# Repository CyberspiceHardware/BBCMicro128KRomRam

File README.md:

# 128K Sideways ROM/RAM expansion for the BBC Micro

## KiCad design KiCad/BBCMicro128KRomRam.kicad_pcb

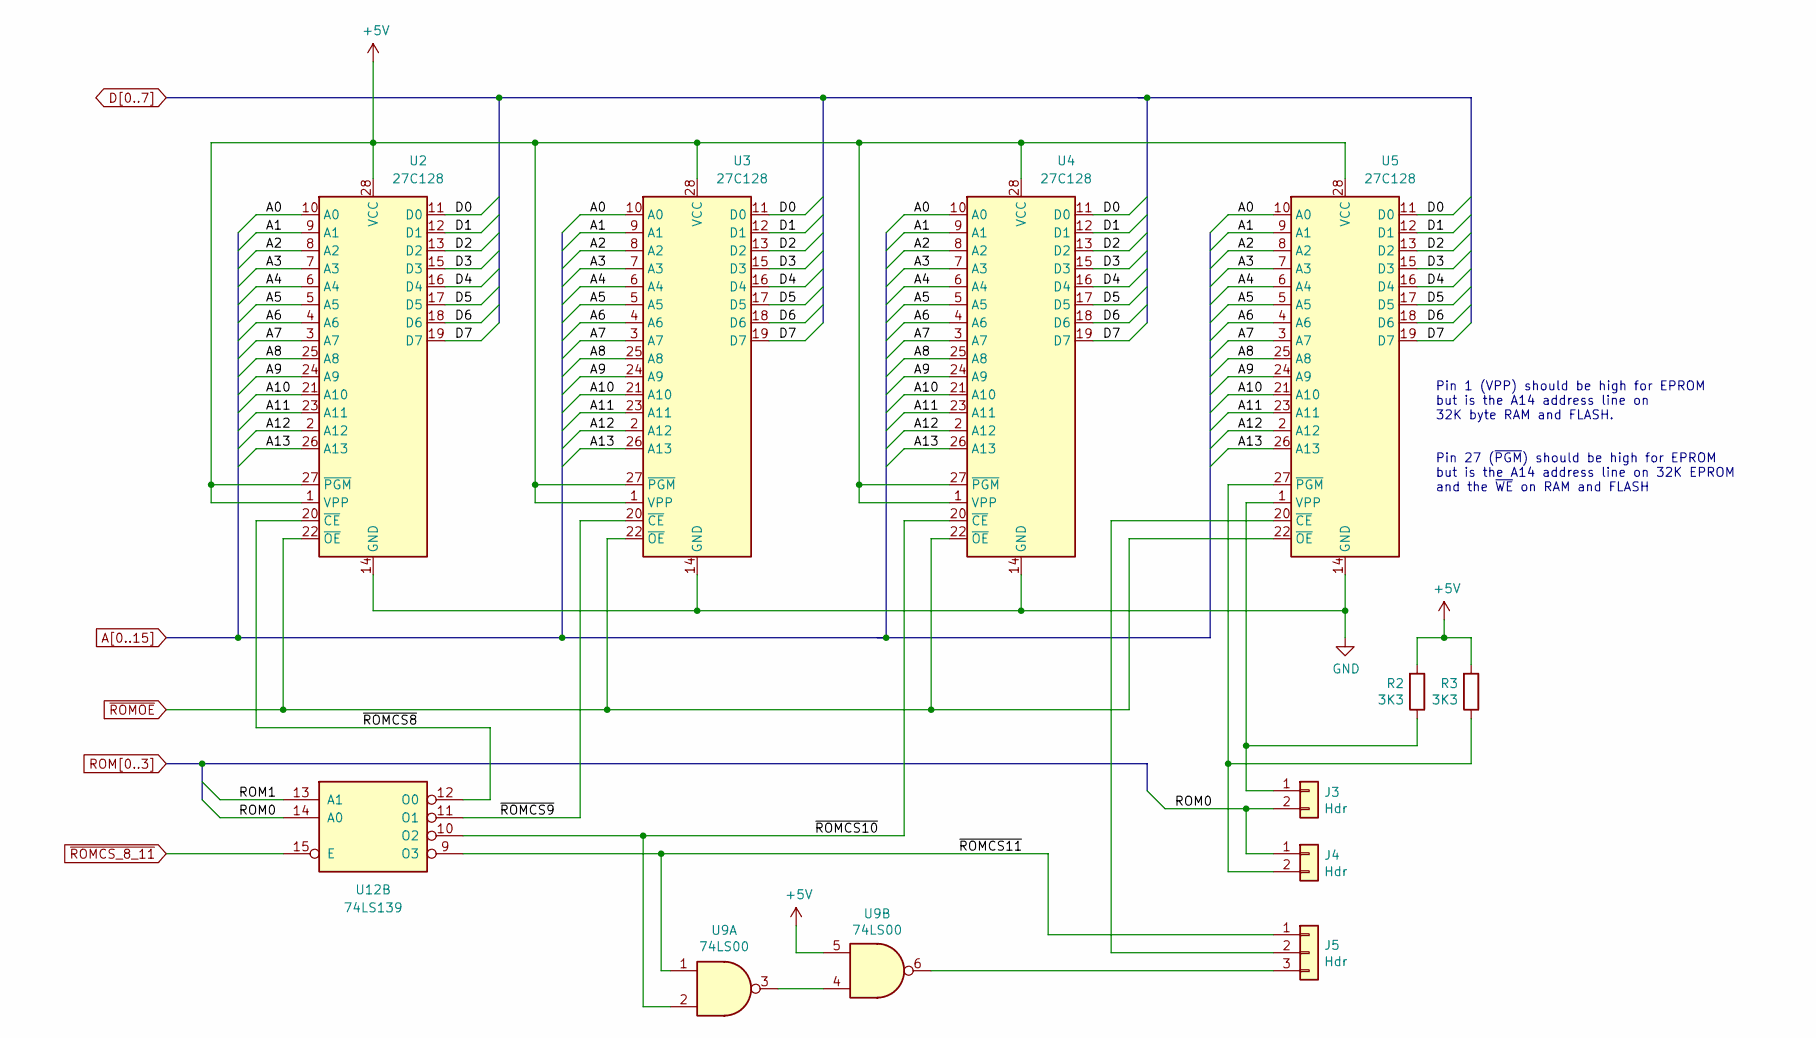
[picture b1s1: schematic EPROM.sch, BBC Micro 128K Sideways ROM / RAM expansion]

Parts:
J3, J4: Hdr; PinHeader_1x02_P2.54mm_Vertical
J5: Hdr; PinHeader_1x03_P2.54mm_Vertical
R2, R3: 3K3; R_Axial_DIN0207_L6.3mm_D2.5mm_P7.62mm_Horizontal
U2, U3, U4, U5: 27C128; DIP-28_W15.24mm_Socket
U9: 74LS00; DIP-14_W7.62mm_Socket
U12: 74LS139

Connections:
+5V: R2.2, R3.2, U2.1 (VPP), U2.27 (~PGM), U2.28 (VCC), U3.1 (VPP), U3.27 (~PGM), U3.28 (VCC), U4.1 (VPP), U4.27 (~PGM), U4.28 (VCC), U5.28 (VCC), U9.5; also elsewhere on the board
/EPROM/~ROMCS8: U2.20 (~CE), U12.12 (O0)
/EPROM/~ROMCS9: U3.20 (~CE), U12.11 (O1)
/EPROM/~ROMCS10: U4.20 (~CE), U9.2, U12.10 (O2)
/EPROM/~ROMCS11: J5.1, U9.1, U12.9 (O3)
A0: U2.10 (A0), U3.10 (A0), U4.10 (A0), U5.10 (A0); also elsewhere on the board
A1: U2.9 (A1), U3.9 (A1), U4.9 (A1), U5.9 (A1); also elsewhere on the board
A2: U2.8 (A2), U3.8 (A2), U4.8 (A2), U5.8 (A2); also elsewhere on the board
A3: U2.7 (A3), U3.7 (A3), U4.7 (A3), U5.7 (A3); also elsewhere on the board
A4: U2.6 (A4), U3.6 (A4), U4.6 (A4), U5.6 (A4); also elsewhere on the board
A5: U2.5 (A5), U3.5 (A5), U4.5 (A5), U5.5 (A5); also elsewhere on the board
A6: U2.4 (A6), U3.4 (A6), U4.4 (A6), U5.4 (A6); also elsewhere on the board
A7: U2.3 (A7), U3.3 (A7), U4.3 (A7), U5.3 (A7); also elsewhere on the board
A8: U2.25 (A8), U3.25 (A8), U4.25 (A8), U5.25 (A8); also elsewhere on the board
A9: U2.24 (A9), U3.24 (A9), U4.24 (A9), U5.24 (A9); also elsewhere on the board
A10: U2.21 (A10), U3.21 (A10), U4.21 (A10), U5.21 (A10); also elsewhere on the board
A11: U2.23 (A11), U3.23 (A11), U4.23 (A11), U5.23 (A11); also elsewhere on the board
A12: U2.2 (A12), U3.2 (A12), U4.2 (A12), U5.2 (A12); also elsewhere on the board
A13: U2.26 (A13), U3.26 (A13), U4.26 (A13), U5.26 (A13); also elsewhere on the board
D0: U2.11 (D0), U3.11 (D0), U4.11 (D0), U5.11 (D0); also elsewhere on the board
D1: U2.12 (D1), U3.12 (D1), U4.12 (D1), U5.12 (D1); also elsewhere on the board
D2: U2.13 (D2), U3.13 (D2), U4.13 (D2), U5.13 (D2); also elsewhere on the board
D3: U2.15 (D3), U3.15 (D3), U4.15 (D3), U5.15 (D3); also elsewhere on the board
D4: U2.16 (D4), U3.16 (D4), U4.16 (D4), U5.16 (D4); also elsewhere on the board
D5: U2.17 (D5), U3.17 (D5), U4.17 (D5), U5.17 (D5); also elsewhere on the board
D6: U2.18 (D6), U3.18 (D6), U4.18 (D6), U5.18 (D6); also elsewhere on the board
D7: U2.19 (D7), U3.19 (D7), U4.19 (D7), U5.19 (D7); also elsewhere on the board
GND: U2.14 (GND), U3.14 (GND), U4.14 (GND), U5.14 (GND); also elsewhere on the board
unnamed: J3.1, R2.1, U5.1 (VPP)
unnamed: J4.2, R3.1, U5.27 (~PGM)
unnamed: J5.2, U5.20 (~CE)
unnamed: J5.3, U9.6
unnamed: U9.3, U9.4
ROM0: J3.2, J4.1, U12.14 (A0); also elsewhere on the board
ROM1: U12.13 (A1); also elsewhere on the board
~ROMCS_8_11: U12.15 (E); also elsewhere on the board
~ROMOE: U2.22 (~OE), U3.22 (~OE), U4.22 (~OE), U5.22 (~OE); also elsewhere on the board

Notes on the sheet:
Pin 1 (VPP) should be high for EPROM but is the A14 address line on 32K byte RAM and FLASH.
Pin 27 (~PGM~) should be high for EPROM but is the A14 address line on 32K EPROM and the ~WE~ on RAM and FLASH

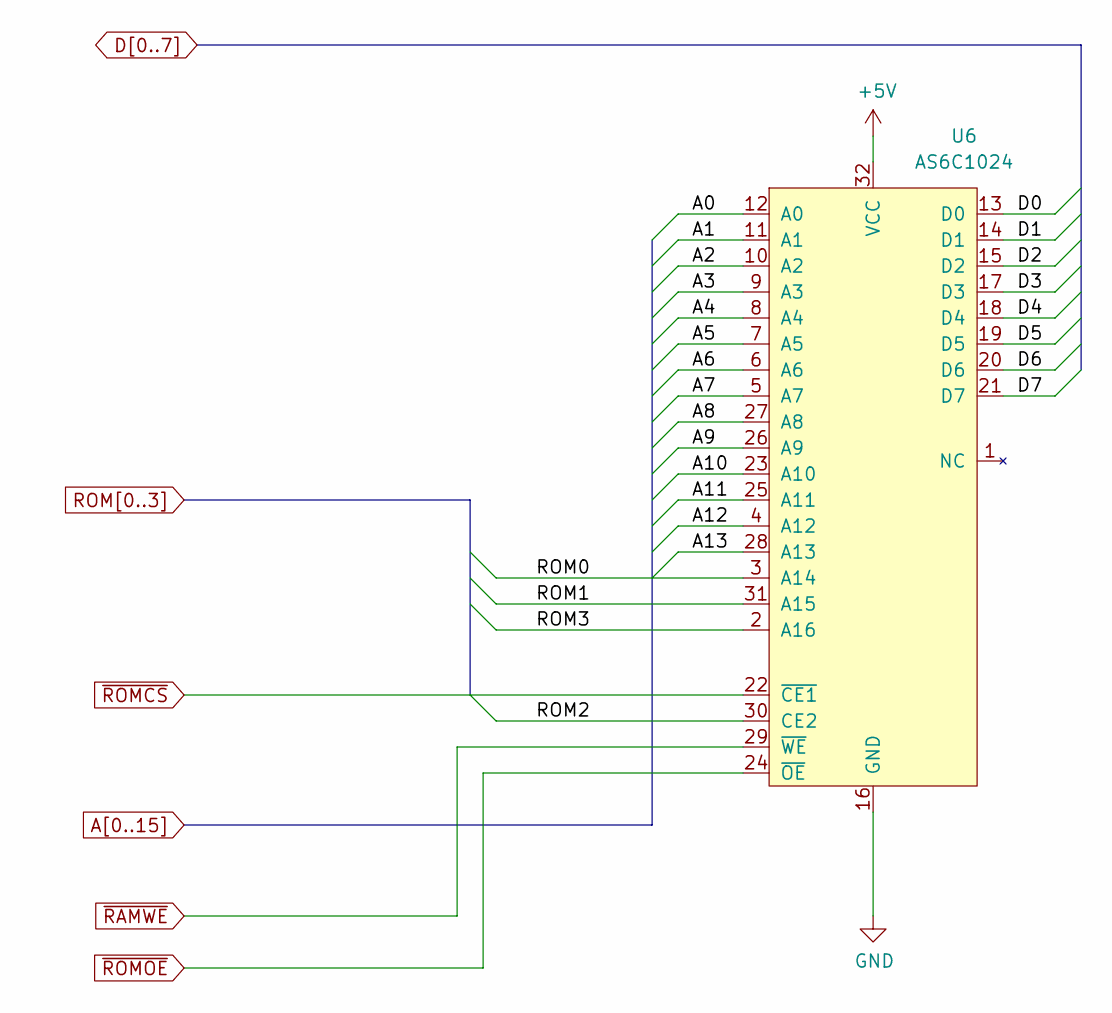
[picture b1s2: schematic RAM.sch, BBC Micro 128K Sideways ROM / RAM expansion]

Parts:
U6: AS6C1024; DIP-32_W15.24mm_Socket

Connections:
+5V: U6.32 (VCC); also elsewhere on the board
A0: U6.12 (A0); also elsewhere on the board
A1: U6.11 (A1); also elsewhere on the board
A2: U6.10 (A2); also elsewhere on the board
A3: U6.9 (A3); also elsewhere on the board
A4: U6.8 (A4); also elsewhere on the board
A5: U6.7 (A5); also elsewhere on the board
A6: U6.6 (A6); also elsewhere on the board
A7: U6.5 (A7); also elsewhere on the board
A8: U6.27 (A8); also elsewhere on the board
A9: U6.26 (A9); also elsewhere on the board
A10: U6.23 (A10); also elsewhere on the board
A11: U6.25 (A11); also elsewhere on the board
A12: U6.4 (A12); also elsewhere on the board
A13: U6.28 (A13); also elsewhere on the board
D0: U6.13 (D0); also elsewhere on the board
D1: U6.14 (D1); also elsewhere on the board
D2: U6.15 (D2); also elsewhere on the board
D3: U6.17 (D3); also elsewhere on the board
D4: U6.18 (D4); also elsewhere on the board
D5: U6.19 (D5); also elsewhere on the board
D6: U6.20 (D6); also elsewhere on the board
D7: U6.21 (D7); also elsewhere on the board
GND: U6.16 (GND); also elsewhere on the board
ROM0: U6.3 (A14); also elsewhere on the board
ROM1: U6.31 (A15); also elsewhere on the board
ROM2: U6.30 (CE2); also elsewhere on the board
ROM3: U6.2 (A16); also elsewhere on the board
~RAMWE: U6.29 (~WE); also elsewhere on the board
~ROMCS: U6.22 (~CE1); also elsewhere on the board
~ROMOE: U6.24 (~OE); also elsewhere on the board

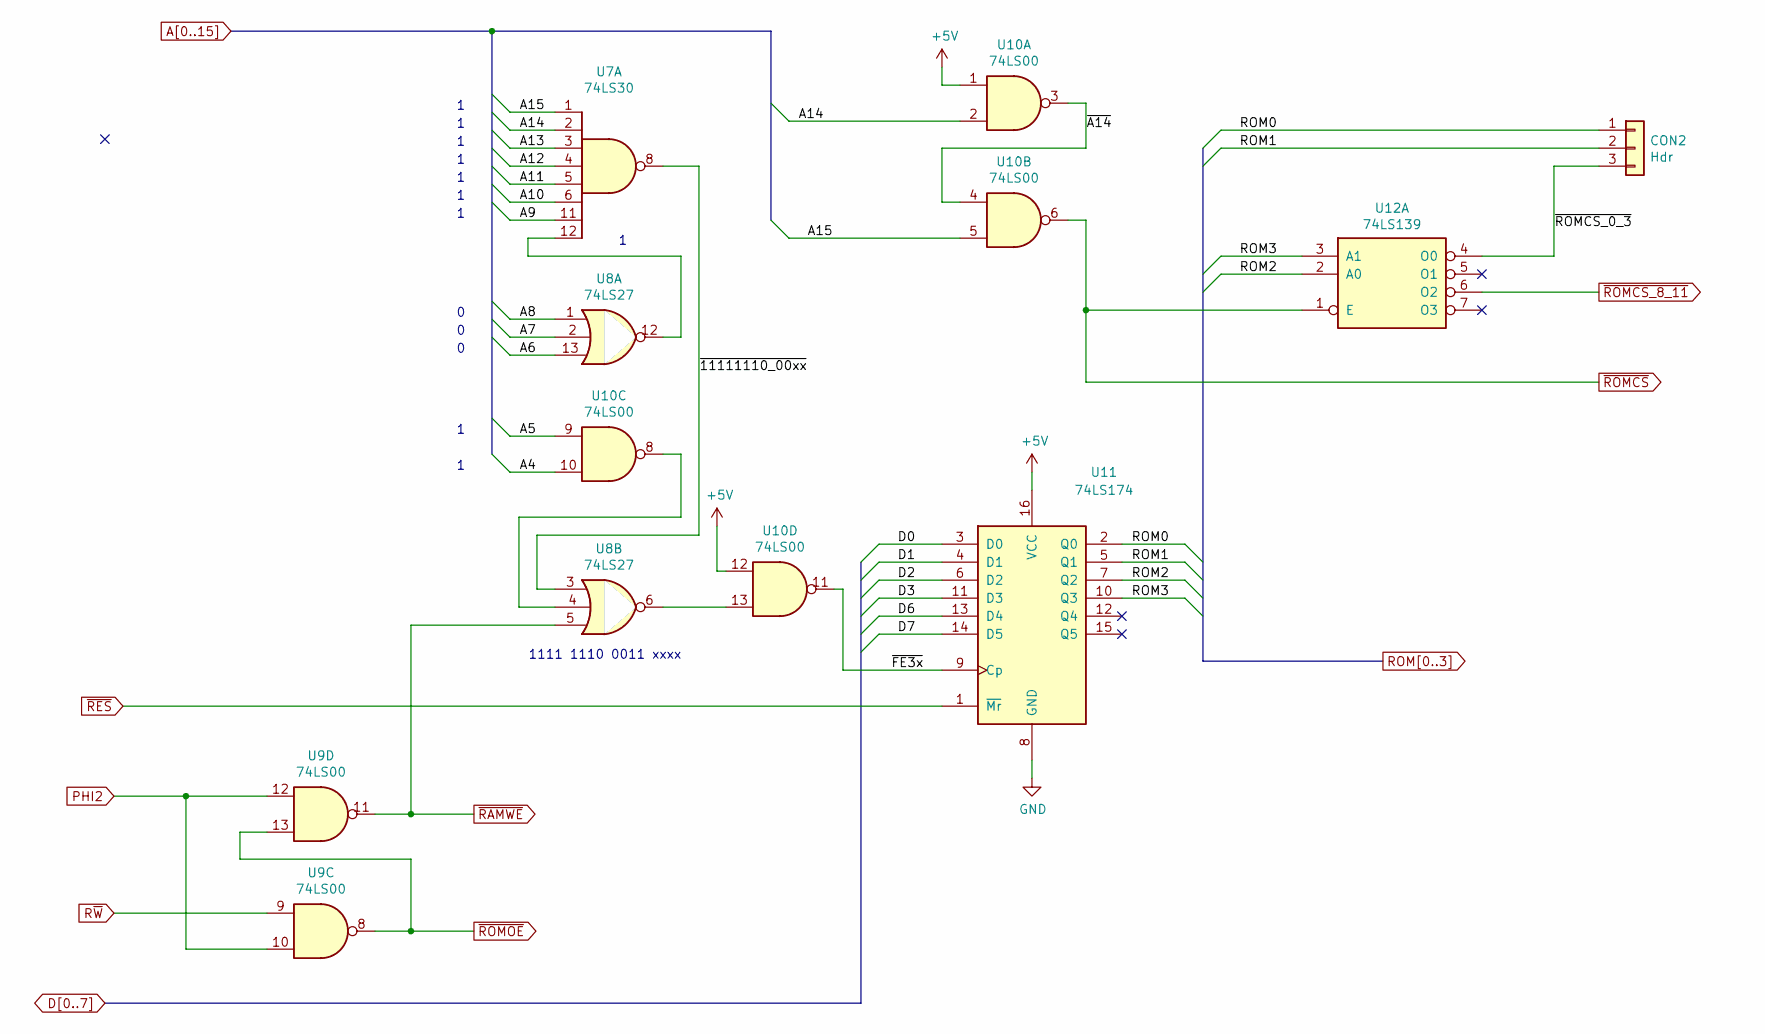
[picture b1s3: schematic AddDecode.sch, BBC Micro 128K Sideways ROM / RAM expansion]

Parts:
CON2: Hdr; PinHeader_1x03_P2.54mm_Horizontal
U7: 74LS30; DIP-14_W7.62mm_Socket
U8: 74LS27; DIP-14_W7.62mm_Socket
U9, U10: 74LS00; DIP-14_W7.62mm_Socket
U11: 74LS174; DIP-16_W7.62mm_Socket
U12: 74LS139; DIP-16_W7.62mm_Socket

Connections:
+5V: U10.1, U10.12, U11.16 (VCC); also elsewhere on the board
/AddDecode/~11111110_00xx: U7.8, U8.3
/AddDecode/~A14: U10.3, U10.4
/AddDecode/~FE3x: U10.11, U11.9 (Cp)
/AddDecode/~ROMCS_0_3: CON2.3, U12.4 (O0)
A4: U10.10; also elsewhere on the board
A5: U10.9; also elsewhere on the board
A6: U8.13; also elsewhere on the board
A7: U8.2; also elsewhere on the board
A8: U8.1; also elsewhere on the board
A9: U7.11; also elsewhere on the board
A10: U7.6; also elsewhere on the board
A11: U7.5; also elsewhere on the board
A12: U7.4; also elsewhere on the board
A13: U7.3; also elsewhere on the board
A14: U7.2, U10.2; also elsewhere on the board
A15: U7.1, U10.5; also elsewhere on the board
D0: U11.3 (D0); also elsewhere on the board
D1: U11.4 (D1); also elsewhere on the board
D2: U11.6 (D2); also elsewhere on the board
D3: U11.11 (D3); also elsewhere on the board
D6: U11.13 (D4); also elsewhere on the board
D7: U11.14 (D5); also elsewhere on the board
GND: U11.8 (GND); also elsewhere on the board
unnamed: U7.12, U8.12
unnamed: U8.4, U10.8
unnamed: U8.6, U10.13
PHI2: U9.10, U9.12; also elsewhere on the board
ROM0: CON2.1, U11.2 (Q0); also elsewhere on the board
ROM1: CON2.2, U11.5 (Q1); also elsewhere on the board
ROM2: U11.7 (Q2), U12.2 (A0); also elsewhere on the board
ROM3: U11.10 (Q3), U12.3 (A1); also elsewhere on the board
R~W: U9.9; also elsewhere on the board
~RAMWE: U8.5, U9.11; also elsewhere on the board
~RES: U11.1 (~Mr); also elsewhere on the board
~ROMCS: U10.6, U12.1 (E); also elsewhere on the board
~ROMCS_8_11: U12.6 (O2); also elsewhere on the board
~ROMOE: U9.8, U9.13; also elsewhere on the board

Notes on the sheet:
1111 1110 0011 xxxx

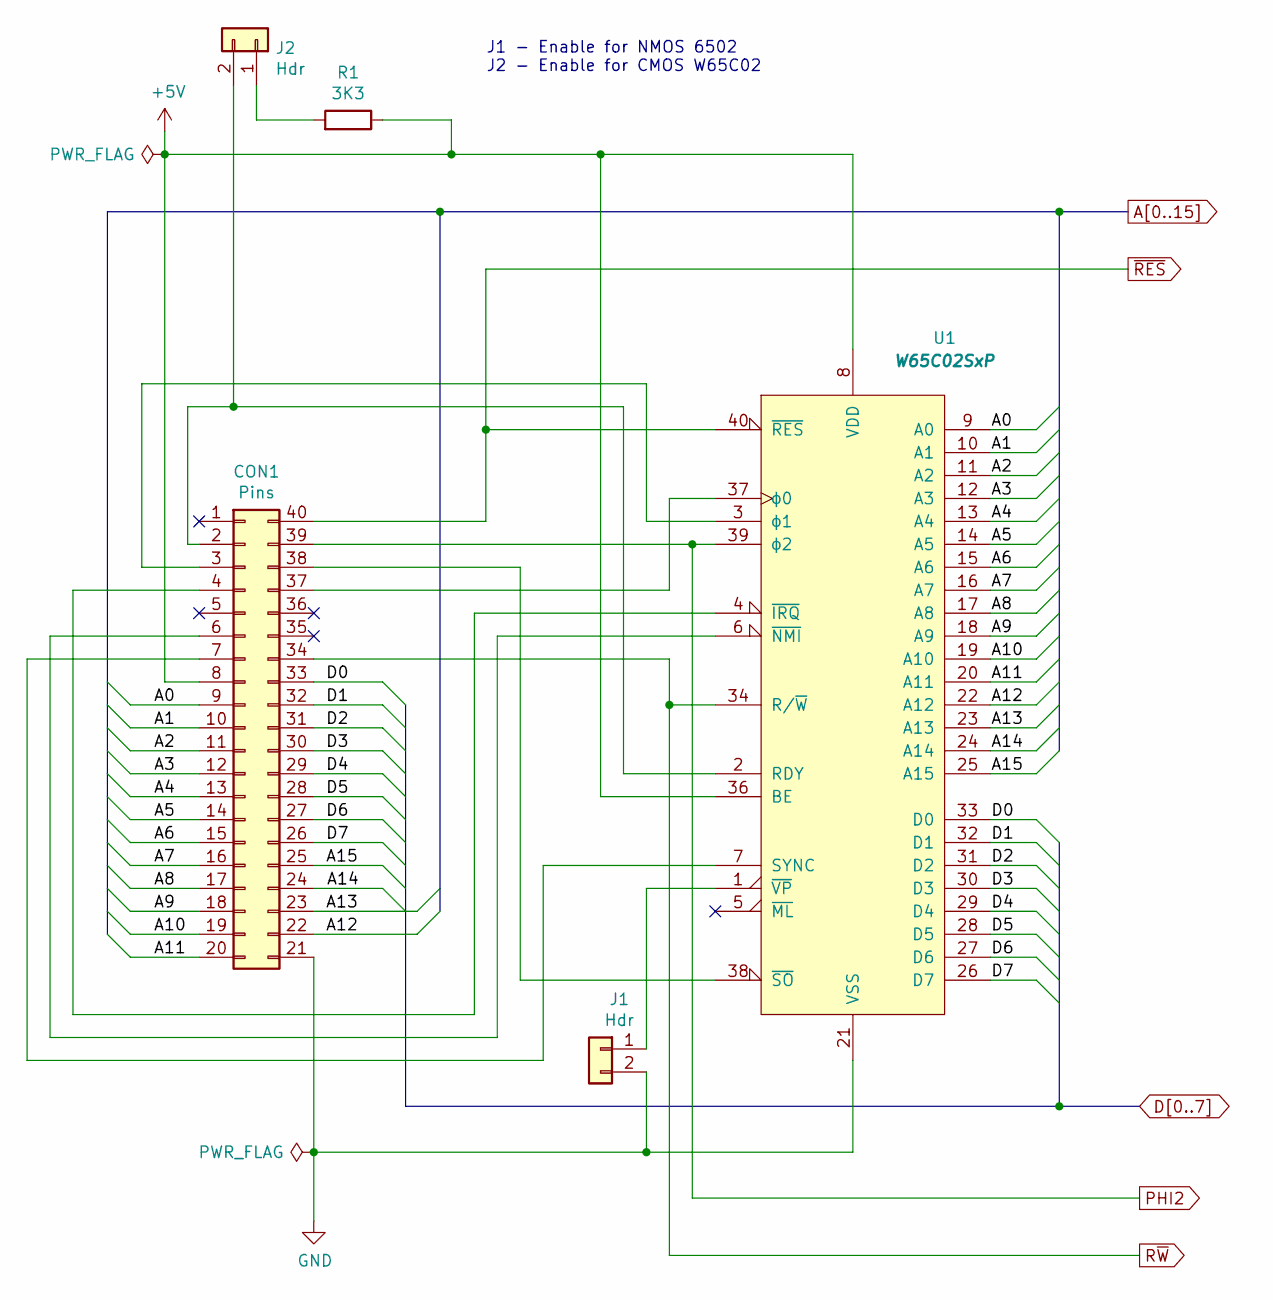
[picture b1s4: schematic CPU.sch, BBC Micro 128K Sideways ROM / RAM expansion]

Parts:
CON1: Pins; DIP-40_W15.24mm_Socket
J1, J2: Hdr; PinHeader_1x02_P2.54mm_Vertical
R1: 3K3; R_Axial_DIN0207_L6.3mm_D2.5mm_P7.62mm_Horizontal
U1: W65C02SxP; DIP-40_W15.24mm_Socket

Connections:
+5V: CON1.8, R1.1, U1.8 (VDD), U1.36 (BE); also elsewhere on the board
A0: CON1.9, U1.9 (A0); also elsewhere on the board
A1: CON1.10, U1.10 (A1); also elsewhere on the board
A2: CON1.11, U1.11 (A2); also elsewhere on the board
A3: CON1.12, U1.12 (A3); also elsewhere on the board
A4: CON1.13, U1.13 (A4); also elsewhere on the board
A5: CON1.14, U1.14 (A5); also elsewhere on the board
A6: CON1.15, U1.15 (A6); also elsewhere on the board
A7: CON1.16, U1.16 (A7); also elsewhere on the board
A8: CON1.17, U1.17 (A8); also elsewhere on the board
A9: CON1.18, U1.18 (A9); also elsewhere on the board
A10: CON1.19, U1.19 (A10); also elsewhere on the board
A11: CON1.20, U1.20 (A11); also elsewhere on the board
A12: CON1.22, U1.22 (A12); also elsewhere on the board
A13: CON1.23, U1.23 (A13); also elsewhere on the board
A14: CON1.24, U1.24 (A14); also elsewhere on the board
A15: CON1.25, U1.25 (A15); also elsewhere on the board
D0: CON1.33, U1.33 (D0); also elsewhere on the board
D1: CON1.32, U1.32 (D1); also elsewhere on the board
D2: CON1.31, U1.31 (D2); also elsewhere on the board
D3: CON1.30, U1.30 (D3); also elsewhere on the board
D4: CON1.29, U1.29 (D4); also elsewhere on the board
D5: CON1.28, U1.28 (D5); also elsewhere on the board
D6: CON1.27, U1.27 (D6); also elsewhere on the board
D7: CON1.26, U1.26 (D7); also elsewhere on the board
GND: CON1.21, J1.2, U1.21 (VSS); also elsewhere on the board
unnamed: CON1.2, J2.2, U1.2 (RDY)
unnamed: CON1.3, U1.3 (ϕ1)
unnamed: CON1.4, U1.4 (~IRQ)
unnamed: CON1.6, U1.6 (~NMI)
unnamed: CON1.7, U1.7 (SYNC)
unnamed: CON1.37, U1.37 (ϕ0)
unnamed: CON1.38, U1.38 (~SO)
unnamed: J1.1, U1.1 (~VP)
unnamed: J2.1, R1.2
PHI2: CON1.39, U1.39 (ϕ2); also elsewhere on the board
R~W: CON1.34, U1.34 (R/~W); also elsewhere on the board
~RES: CON1.40, U1.40 (~RES); also elsewhere on the board

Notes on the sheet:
J1 - Enable for NMOS 6502 J2 - Enable for CMOS W65C02

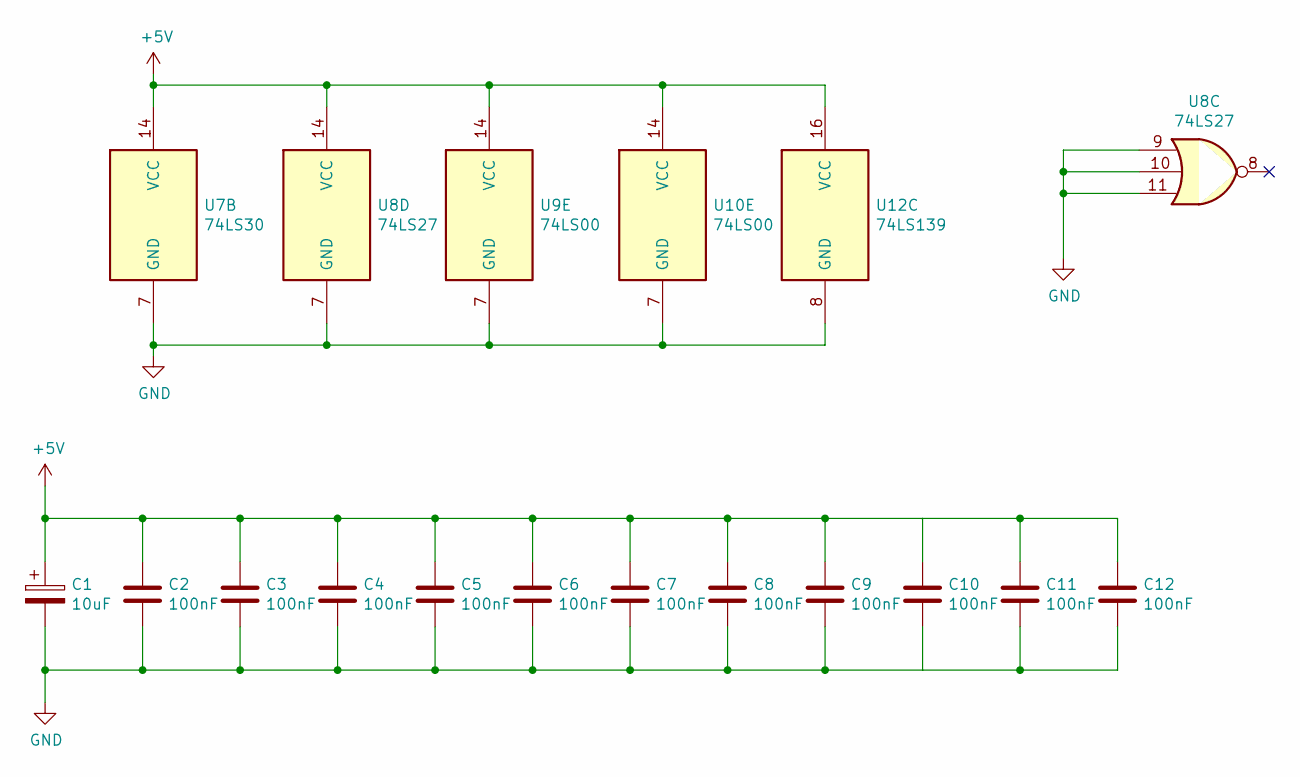
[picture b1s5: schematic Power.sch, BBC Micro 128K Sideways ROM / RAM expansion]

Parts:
C1: 10uF; CP_Radial_D5.0mm_P2.50mm
C2, C3, C4, C5, C6, C7, C8, C9, C10, C11, C12: 100nF; C_Disc_D7.5mm_W2.5mm_P5.00mm
U7: 74LS30; DIP-14_W7.62mm_Socket
U8: 74LS27; DIP-14_W7.62mm_Socket
U9, U10: 74LS00; DIP-14_W7.62mm_Socket
U12: 74LS139; DIP-16_W7.62mm_Socket

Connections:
+5V: C1.1, C2.1, C3.1, C4.1, C5.1, C6.1, C7.1, C8.1, C9.1, C10.1, C11.1, C12.1, U7.14 (VCC), U8.14 (VCC), U9.14 (VCC), U10.14 (VCC), U12.16 (VCC); also elsewhere on the board
GND: C1.2, C2.2, C3.2, C4.2, C5.2, C6.2, C7.2, C8.2, C9.2, C10.2, C11.2, C12.2, U7.7 (GND), U8.7 (GND), U8.9, U8.10, U8.11, U9.7 (GND), U10.7 (GND), U12.8 (GND); also elsewhere on the board

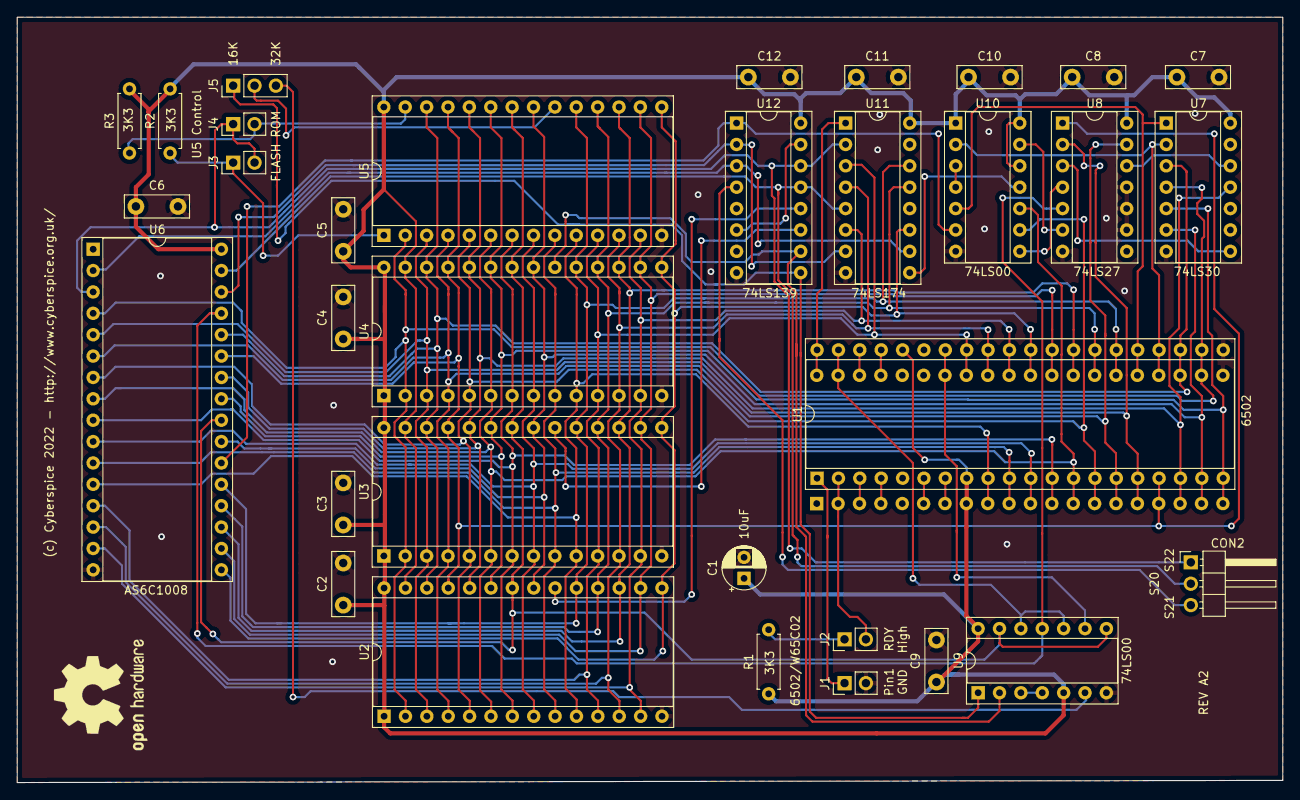
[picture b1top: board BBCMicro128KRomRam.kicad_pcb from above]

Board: 2 copper layers, 150.4 x 90.9 mm, 34 parts (0 on the bottom side), 62 nets.

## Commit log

2022-05-22 Fixed some typos and centralised board layout
